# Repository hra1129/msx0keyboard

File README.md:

新プロトコルに関しては、MSX0に採用されるかどうかも分かりませんし、現時点のバージョンではサポートされていませんので、
新バージョンの方は使える環境はありません。未テストです。

キーボードに付いている Grove端子には、プルアップ抵抗(3.3kΩ)を付けなければ機能しません。
G32とG33の二カ所を 3.3kΩ経由で 5V に繋いでください。

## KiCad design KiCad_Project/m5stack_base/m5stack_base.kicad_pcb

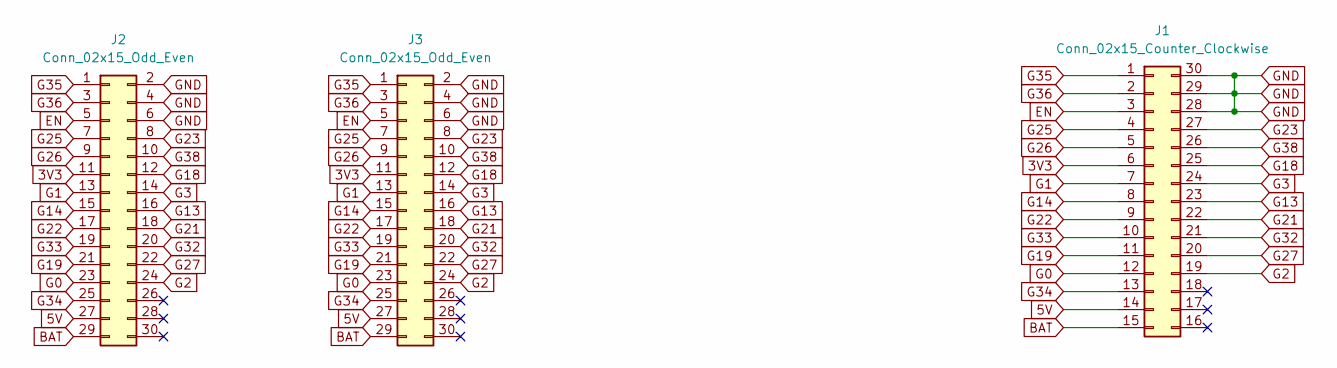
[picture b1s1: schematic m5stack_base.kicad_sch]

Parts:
J1: Conn_02x15_Counter_Clockwise; M5StackBase2_1
J2, J3: Conn_02x15_Odd_Even; PinHeader_2x15_P2.54mm_Vertical

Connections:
3V3: J1.6, J2.11, J3.11
5V: J1.14, J2.27, J3.27
BAT: J1.15, J2.29, J3.29
EN: J1.3, J2.5, J3.5
G0: J1.12, J2.23, J3.23
G1: J1.7, J2.13, J3.13
G2: J1.19, J2.24, J3.24
G3: J1.24, J2.14, J3.14
G13: J1.23, J2.16, J3.16
G14: J1.8, J2.15, J3.15
G18: J1.25, J2.12, J3.12
G19: J1.11, J2.21, J3.21
G21: J1.22, J2.18, J3.18
G22: J1.9, J2.17, J3.17
G23: J1.27, J2.8, J3.8
G25: J1.4, J2.7, J3.7
G26: J1.5, J2.9, J3.9
G27: J1.20, J2.22, J3.22
G32: J1.21, J2.20, J3.20
G33: J1.10, J2.19, J3.19
G34: J1.13, J2.25, J3.25
G35: J1.1, J2.1, J3.1
G36: J1.2, J2.3, J3.3
G38: J1.26, J2.10, J3.10
GND: J1.28, J1.29, J1.30, J2.2, J2.4, J2.6, J3.2, J3.4, J3.6

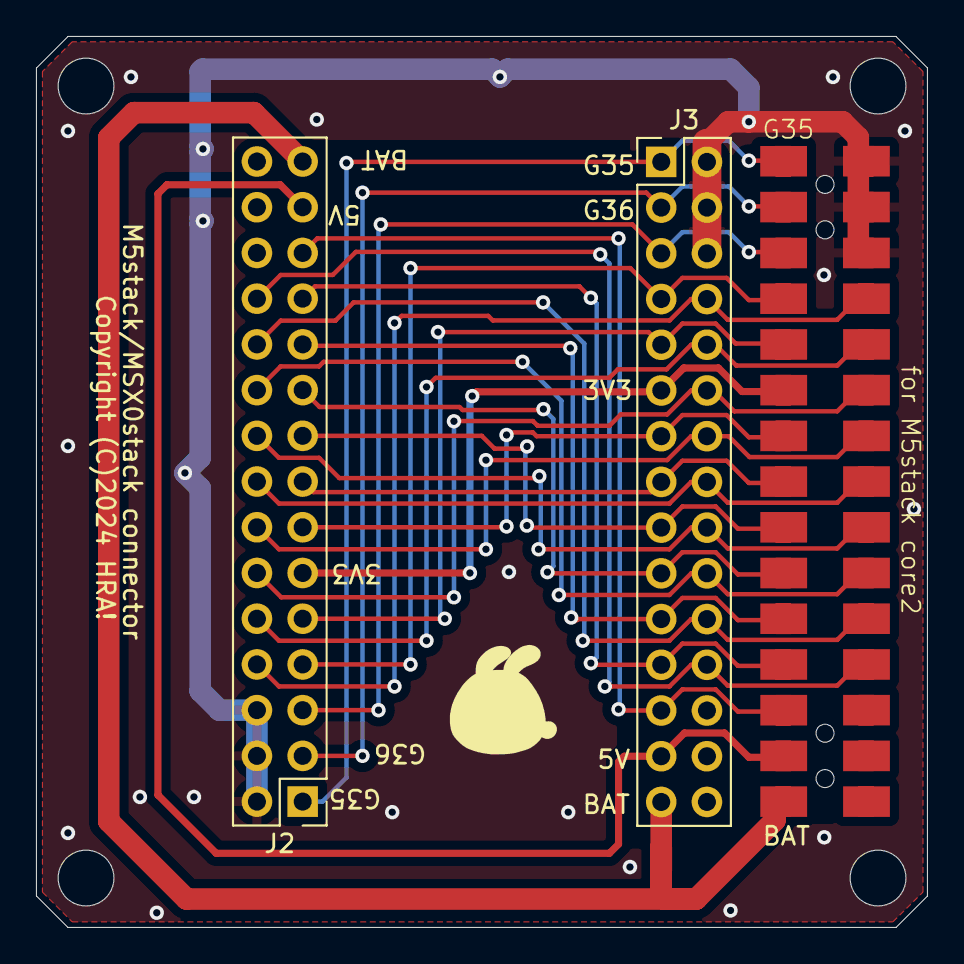
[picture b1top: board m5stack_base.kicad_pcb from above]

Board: 2 copper layers, 49.5 x 49.5 mm, 3 parts (0 on the bottom side), 25 nets.

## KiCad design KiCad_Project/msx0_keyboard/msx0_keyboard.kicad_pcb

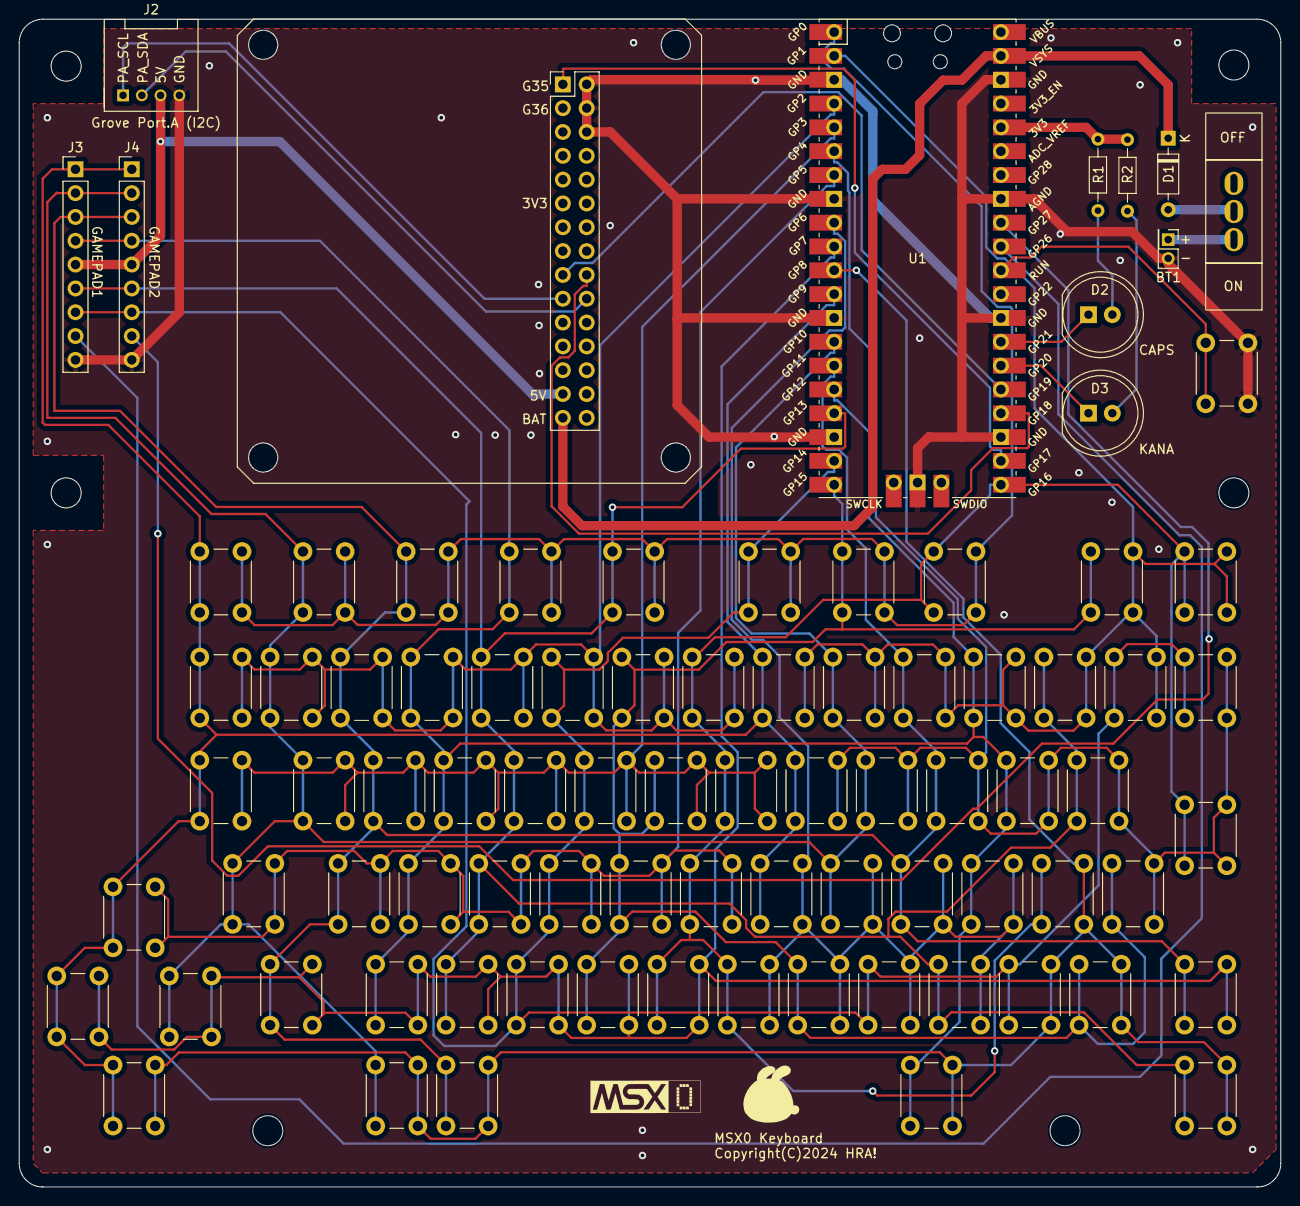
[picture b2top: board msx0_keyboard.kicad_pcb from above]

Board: 2 copper layers, 134.5 x 124.5 mm, 93 parts (0 on the bottom side), 35 nets.

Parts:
BT1: Battery_Cell; PinHeader_2x01_P2.00mm_Vertical
D1: 1N914; D_DO-35_SOD27_P7.62mm_Horizontal
D2, D3: LED; LED_D8.0mm
HOLE0, HOLE1, HOLE2, HOLE3, HOLE4, HOLE5: MountingHole_3.2mm_M3
J1: M5stack Connector; M5StackConnect
J2: Conn_01x04_Pin; HW4-2.0-90D
J3, J4: DE9_Plug; PinHeader_1x09_P2.54mm_Vertical
MSX0: LOGO; MSX0_logo_15mm
R1, R2: R; R_Axial_DIN0204_L3.6mm_D1.6mm_P7.62mm_Horizontal
SW1: F1; SW_PUSH_6mm
SW2: F2; SW_PUSH_6mm
SW3: F3; SW_PUSH_6mm
SW4: F4; SW_PUSH_6mm
SW5: F5; SW_PUSH_6mm
SW6: STOP; SW_PUSH_6mm
SW7: CLS; SW_PUSH_6mm
SW8: SELECT; SW_PUSH_6mm
SW9: INS; SW_PUSH_6mm
SW10: DEL; SW_PUSH_6mm
SW11: ESC; SW_PUSH_6mm
SW12: 1; SW_PUSH_6mm
SW13: 2; SW_PUSH_6mm
SW14: 3; SW_PUSH_6mm
SW15: 4; SW_PUSH_6mm
SW16: 5; SW_PUSH_6mm
SW17: 6; SW_PUSH_6mm
SW18: 7; SW_PUSH_6mm
SW19: 8; SW_PUSH_6mm
SW20: 9; SW_PUSH_6mm
SW21: 0; SW_PUSH_6mm
SW22: -; SW_PUSH_6mm
SW23: ^; SW_PUSH_6mm
SW24: ￥; SW_PUSH_6mm
SW25: BS; SW_PUSH_6mm
SW26: TAB; SW_PUSH_6mm
SW27: Q; SW_PUSH_6mm
SW28: W; SW_PUSH_6mm
SW29: E; SW_PUSH_6mm
SW30: R; SW_PUSH_6mm
SW31: T; SW_PUSH_6mm
SW32: Y; SW_PUSH_6mm
SW33: U; SW_PUSH_6mm
SW34: I; SW_PUSH_6mm
SW35: O; SW_PUSH_6mm
SW36: P; SW_PUSH_6mm
SW37: @; SW_PUSH_6mm
SW38: [; SW_PUSH_6mm
SW39: RETURN; SW_PUSH_6mm
SW40: CTRL; SW_PUSH_6mm
SW41: A; SW_PUSH_6mm
SW42: S; SW_PUSH_6mm
SW43: D; SW_PUSH_6mm
SW44: F; SW_PUSH_6mm
SW45: G; SW_PUSH_6mm
SW46: H; SW_PUSH_6mm
SW47: J; SW_PUSH_6mm
SW48: K; SW_PUSH_6mm
SW49: L; SW_PUSH_6mm
SW50: ;; SW_PUSH_6mm
SW51: :; SW_PUSH_6mm
SW52: ]; SW_PUSH_6mm
SW53, SW65: SHIFT; SW_PUSH_6mm
SW54: Z; SW_PUSH_6mm
SW55: X; SW_PUSH_6mm
SW56: C; SW_PUSH_6mm
SW57: V; SW_PUSH_6mm
SW58: B; SW_PUSH_6mm
SW59: N; SW_PUSH_6mm
SW60: M; SW_PUSH_6mm
SW61: ,; SW_PUSH_6mm
SW62: .; SW_PUSH_6mm
SW63: /; SW_PUSH_6mm
SW64: _; SW_PUSH_6mm
SW66: CAPS; SW_PUSH_6mm
SW67: GRPH; SW_PUSH_6mm
SW68: SPACE; SW_PUSH_6mm
SW69: KANA; SW_PUSH_6mm
SW70: ←; SW_PUSH_6mm
SW71: →; SW_PUSH_6mm
SW72: ↑; SW_PUSH_6mm
SW73: ↓; SW_PUSH_6mm
SW74: SW_MEC_5G; SW_PUSH_6mm
SW75: SW_SPST; Slide Switch
U1: Pico; RPi_Pico_SMD_TH

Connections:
/BAT: D1.1 (K), J1.29, U1.39 (VSYS)
GND: BT1.2 (-), J1.2, J1.4, J1.6, J2.4, J3.9, J4.9, SW74.2 (A), U1.3 (GND), U1.8 (GND), U1.13 (GND), U1.18 (GND), U1.23 (GND), U1.28 (GND), U1.33 (AGND), U1.38 (GND), U1.42 (GND)
INT_SCL: J1.17, U1.25 (GPIO19)
INT_SDA: J1.18, U1.24 (GPIO18)
KEY_INT: J1.1, U1.22 (GPIO17)
unnamed: BT1.1 (+), SW75.1 (A)
unnamed: D1.2 (A), SW75.2 (B)
unnamed: D2.2 (A), R1.1
unnamed: D2.1 (K), U1.27 (GPIO21)
unnamed: D3.2 (A), R2.1
unnamed: D3.1 (K), U1.26 (GPIO20)
unnamed: R1.2, R2.2, U1.36 (3V3)
unnamed: SW74.1 (A), U1.30 (RUN)
PA_5V: J1.27, J2.3, J3.5, J4.5
PA_SCL: J1.19, J2.1
PA_SDA: J1.20, J2.2
X0: J3.1, J4.1, SW1.1, SW11.1, SW19.1, SW26.1, SW34.1, SW47.1, SW70.1, SW72.1, SW73.1, U1.12 (GPIO9)
X1: J3.2, J4.2, SW2.1, SW12.1, SW20.1, SW27.1, SW35.1, SW40.1, SW48.1, SW66.1, SW71.1, U1.14 (GPIO10)
X2: J3.3, J4.3, SW3.1, SW13.1, SW21.1, SW28.1, SW36.1, SW41.1, SW49.1, SW53.1, SW65.1, SW67.1, U1.15 (GPIO11)
X3: J3.4, J4.4, SW4.1, SW14.1, SW22.1, SW29.1, SW37.1, SW42.1, SW50.1, SW54.1, SW68.1, U1.16 (GPIO12)
X4: J3.6, J4.6, SW5.1, SW15.1, SW23.1, SW30.1, SW38.1, SW43.1, SW55.1, SW62.1, SW69.1, U1.17 (GPIO13)
X5: J3.7, J4.7, SW6.1, SW16.1, SW24.1, SW25.1, SW31.1, SW44.1, SW56.1, SW61.1, SW63.1, U1.19 (GPIO14)
X6: SW7.1, SW9.1, SW17.1, SW32.1, SW45.1, SW52.1, SW57.1, SW60.1, SW64.1, U1.20 (GPIO15)
X7: SW8.1, SW10.1, SW18.1, SW33.1, SW39.1, SW46.1, SW51.1, SW58.1, SW59.1, U1.21 (GPIO16)
Y0: SW1.2, SW2.2, SW3.2, SW4.2, SW5.2, SW6.2, SW7.2, SW8.2, U1.1 (GPIO0)
Y1: SW9.2, SW10.2, SW19.2, SW20.2, SW21.2, SW22.2, SW23.2, SW24.2, U1.2 (GPIO1)
Y2: SW11.2, SW12.2, SW13.2, SW14.2, SW15.2, SW16.2, SW17.2, SW18.2, U1.4 (GPIO2)
Y3: SW26.2, SW27.2, SW28.2, SW29.2, SW30.2, SW31.2, SW32.2, SW33.2, U1.5 (GPIO3)
Y4: SW25.2, SW34.2, SW35.2, SW36.2, SW37.2, SW38.2, SW39.2, SW52.2, U1.6 (GPIO4)
Y5: SW40.2, SW41.2, SW42.2, SW43.2, SW44.2, SW45.2, SW46.2, SW72.2, U1.7 (GPIO5)
Y6: SW47.2, SW48.2, SW49.2, SW50.2, SW59.2, SW60.2, SW61.2, SW62.2, U1.9 (GPIO6)
Y7: SW53.2, SW54.2, SW55.2, SW56.2, SW57.2, SW58.2, SW65.2, SW70.2, SW71.2, U1.10 (GPIO7)
Y8: SW51.2, SW63.2, SW64.2, SW66.2, SW67.2, SW68.2, SW69.2, SW73.2, U1.11 (GPIO8)
Y9: J3.8, U1.31 (GPIO26_ADC0)
Y10: J4.8, U1.32 (GPIO27_ADC1)

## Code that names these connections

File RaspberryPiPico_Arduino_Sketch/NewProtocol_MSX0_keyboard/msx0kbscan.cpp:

// --------------------------------------------------------------------
//	MSX0 Keyboard key scan
// ====================================================================
// Copyright 2024 Takayuki Hara
//
//  Permission is hereby granted, free of charge, to any person obtaining 
// a copy of this software and associated documentation files face2keymap, 
// to deal in the Software without restriction, including without limitation 
// the rights to use, copy, modify, merge, publish, distribute, sublicense, 
// and/or sell copies of the Software, and to permit persons to whom the 
// Software is furnished to do so, subject to the following conditions:
//
//  The above copyright notice and this permission notice shall be included 
// in all copies or substantial portions of the Software.
//
//  THE SOFTWARE IS PROVIDED “AS IS”, WITHOUT WARRANTY OF ANY KIND, 
// EXPRESS OR IMPLIED, INCLUDING BUT NOT LIMITED TO THE WARRANTIES OF 
// MERCHANTABILITY, FITNESS FOR A PARTICULAR PURPOSE AND NONINFRINGEMENT. 
//  IN NO EVENT SHALL THE AUTHORS OR COPYRIGHT HOLDERS BE LIABLE FOR ANY 
// CLAIM, DAMAGES OR OTHER LIABILITY, WHETHER IN AN ACTION OF CONTRACT, 
// TORT OR OTHERWISE, ARISING FROM, OUT OF OR IN CONNECTION WITH THE 
// SOFTWARE OR THE USE OR OTHER DEALINGS IN THE SOFTWARE.
// --------------------------------------------------------------------

#include <hardware/gpio.h>
#include <pico/stdlib.h>
#include <cstring>
#include "msx0kbscan.h"

// --------------------------------------------------------------------
//	MSX Keymatrix
//		MSB   7   6   5   4   3   2   1   0    LSB
//		+0   [7 ][6 ][5 ][4 ][3 ][2 ][1 ][0 ]
//		+1   [+ ][{ ][@ ][\ ][^ ][- ][9 ][8 ]
//		+2   [B ][A ][_ ][/ ][. ][, ][} ][* ]
//		+3   [J ][I ][H ][G ][F ][E ][D ][C ]
//		+4   [R ][Q ][P ][O ][N ][M ][L ][K ]
//		+5   [Z ][Y ][X ][W ][V ][U ][T ][S ]
//		+6   [F3][F2][F1][KN][CP][GR][CT][SH]
//		+7   [RT][SE][BS][ST][TB][ES][F5][F4]
//		+8   [RI][DN][UP][LE][DE][IN][HO][SP]
//		+9   [T4][T3][T2][T1][T0][  ][  ][  ]
//		+10  [T,][T.][T-][T9][T8][T7][T6][T5]
//		+11  [  ][  ][A7][A6][A4][A3][A2][A1]    JOYPAD1
//		+12  [  ][  ][B7][B6][B4][B3][B2][B1]    JOYPAD2
//
// --------------------------------------------------------------------
//	Keyboard ROW signals Y0...Y8
//		Y0 : GPIO0
//		Y1 : GPIO1
//		Y2 : GPIO2
//		Y3 : GPIO3
//		Y4 : GPIO4
//		Y5 : GPIO5
//		Y6 : GPIO6
//		Y7 : GPIO7
//		Y8 : GPIO8
//		Y9 : GPIO26
//		Y10: GPIO27
//	Keyboard COLUMN signals X0...X7
//		X0: GPIO9
//		X1: GPIO10
//		X2: GPIO11
//		X3: GPIO12
//		X4: GPIO13
//		X5: GPIO14
//		X6: GPIO15
//		X7: GPIO16
//	Others
//		KEY_INT: GPIO17
//		INT_SCA: GPIO18		※この class では処理しない
//		INT_SCL: GPIO19		※この class では処理しない
//
#define CVT( msx_y, msx_x )		( ((msx_y) << 8) | ((1 << (msx_x)) ^ 0xFF) )
#define CVT_X( convert )		( (convert) & 0xFF )
#define CVT_Y( convert )		( (convert) >> 8 )

//	MSX0 Keyboard のマトリクスから MSXキーマトリクスの ROW/COLUM を得るためのテーブル
static const int convert_table[ /* Y */ ][ 8 /* X */ ] = {
	//    F1        F2        F3        F4        F5        ST        HO        SE
	{ CVT( 6,5),CVT( 6,6),CVT( 6,7),CVT( 7,0),CVT( 7,1),CVT( 7,4),CVT( 8,1),CVT( 7,6) },
	//    9         8         0         -         ^         ￥        IN        DE
	{ CVT( 1,0),CVT( 1,1),CVT( 0,0),CVT( 1,2),CVT( 1,3),CVT( 1,4),CVT( 8,2),CVT( 8,3) },
	//    ES        1         2         3         4         5         6         7
	{ CVT( 7,2),CVT( 0,1),CVT( 0,2),CVT( 0,3),CVT( 0,4),CVT( 0,5),CVT( 0,6),CVT( 0,7) },
	//    TB        Q         W         E         R         T         Y         U
	{ CVT( 7,3),CVT( 4,6),CVT( 5,4),CVT( 4,2),CVT( 4,7),CVT( 5,1),CVT( 5,6),CVT( 5,2) },
	//    I         O         P         @         {         BS        }         RT
	{ CVT( 3,6),CVT( 4,4),CVT( 4,5),CVT( 1,5),CVT( 1,6),CVT( 7,5),CVT( 2,1),CVT( 7,7) },
	//    UP        CT        A         S         D         F         G         H
	{ CVT( 8,5),CVT( 6,1),CVT( 2,6),CVT( 5,0),CVT( 3,1),CVT( 3,3),CVT( 3,4),CVT( 3,5) },
	//    J         K         L         +         .         ,         M         N
	{ CVT( 3,7),CVT( 4,0),CVT( 4,1),CVT( 1,7),CVT( 2,3),CVT( 2,2),CVT( 4,2),CVT( 4,3) },
	//    LE        RI        SH        Z         X         C         V         B
	{ CVT( 8,4),CVT( 8,7),CVT( 6,0),CVT( 5,7),CVT( 5,5),CVT( 3,0),CVT( 5,3),CVT( 2,7) },
	//    DN        CP        GR        SP        KN        /         _         *
	{ CVT( 8,6),CVT( 6,3),CVT( 6,2),CVT( 8,0),CVT( 6,4),CVT( 2,4),CVT( 2,5),CVT( 2,0) },
	//    RSV       RSV       A7        A6        A4        A3        A2        A1
	{ -1,       -1,       CVT(11,5),CVT(11,4),CVT(11,3),CVT(11,2),CVT(11,1),CVT(11,0) },
	//    RSV       RSV       B7        B6        B4        B3        B2        B1
	{ -1,       -1,       CVT(12,5),CVT(12,4),CVT(12,3),CVT(12,2),CVT(12,1),CVT(12,0) },
};

static const int gpio_x[] = { 9, 10, 11, 12, 13, 14, 15, 16 };
static const int gpio_y[] = { 0, 1, 2, 3, 4, 5, 6, 7, 8, 26, 27 };

// ----------------------------------------------------------------
//	begin()
//		Initialization process to use the keyboard.
//		キーボードを利用するための初期化処理。
//
void CMSX0KBSCAN::begin( void ) {
	int i;

	//	全キー押されていない状態にクリア
	std::memset( this->keymatrix, 0xFF, sizeof(this->keymatrix) );

	//	GPIOを初期化する (Y, X)
	for( i = 0; i < sizeof(gpio_x)/sizeof(gpio_x[0]); i++ ) {
		gpio_init( gpio_x[i] );
		gpio_set_dir( gpio_x[i], false );	// input
		gpio_pull_up( gpio_x[i] );			// pull up
	}
	for( i = 0; i < sizeof(gpio_y)/sizeof(gpio_y[0]); i++ ) {
		gpio_init( gpio_y[i] );
		gpio_set_dir( gpio_y[i], false );	// input
		gpio_pull_up( gpio_y[i] );			// pull up
	}
}

// ----------------------------------------------------------------
//	update()
//		Update key matrix information.
//		キーマトリクス情報を更新する。
//
bool CMSX0KBSCAN::update( void ) {
	int x, y, gy;
	uint8_t previous_matrix[ sizeof( this->keymatrix ) ];
	uint32_t keys;
	int convert, msx_y, msx_x;

	//	直前の状態をバックアップ
	std::memcpy( previous_matrix, this->keymatrix, sizeof( this->keymatrix ) );
	//	キー状態を更新
	std::memset( this->keymatrix, 0xFF, sizeof( this->keymatrix ) );
	for( y = 0; y < 11; y++ ) {
		//	ROW を L にする
		gy = gpio_y[y];
		gpio_put( gy, 0 );
		gpio_set_dir( gy, true );	// output
		sleep_us(10);
		//	X を読む
		keys = (gpio_get_all() >> 9) & 0xFF;
		for( x = 0; x < 8; x++ ) {
			if( (keys & 1) == 0 ) {
				//	対応するキーが押されている場合
				convert = convert_table[y][x];
				msx_x = CVT_X( convert );
				msx_y = CVT_Y( convert );
				this->keymatrix[ msx_y ] &= msx_x;
			}
			keys >>= 1;
		}
		//	ROW を HiZ に戻す
		gpio_set_dir( gy, false );	// input
		sleep_us(10);
	}
	for( y = 0; y < 13; y++ ) {
		if( this->keymatrix[ y ] != previous_matrix[ y ] ) return true;
	}
	return false;
}

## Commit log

2024-04-28 Updated
    新ボードの LED に対応。
2024-08-07 Updated
    FaceII 互換モードにおいて、( ) { } [ ] あたりの入力がおかしかったバグを修正。
2024-08-12 組み立て説明書を追加
2024-08-13 Updated
    仮名入力が出来なかった問題を修正

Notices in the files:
KiCad_Project/m5stack_base/m5stack_base.kicad_pcb:
Copyright (C)2024 HRA!
